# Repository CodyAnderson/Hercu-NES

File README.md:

# Hercu-NES
Hardware Exact Rough Clone Unto Nintendo Entertainment System

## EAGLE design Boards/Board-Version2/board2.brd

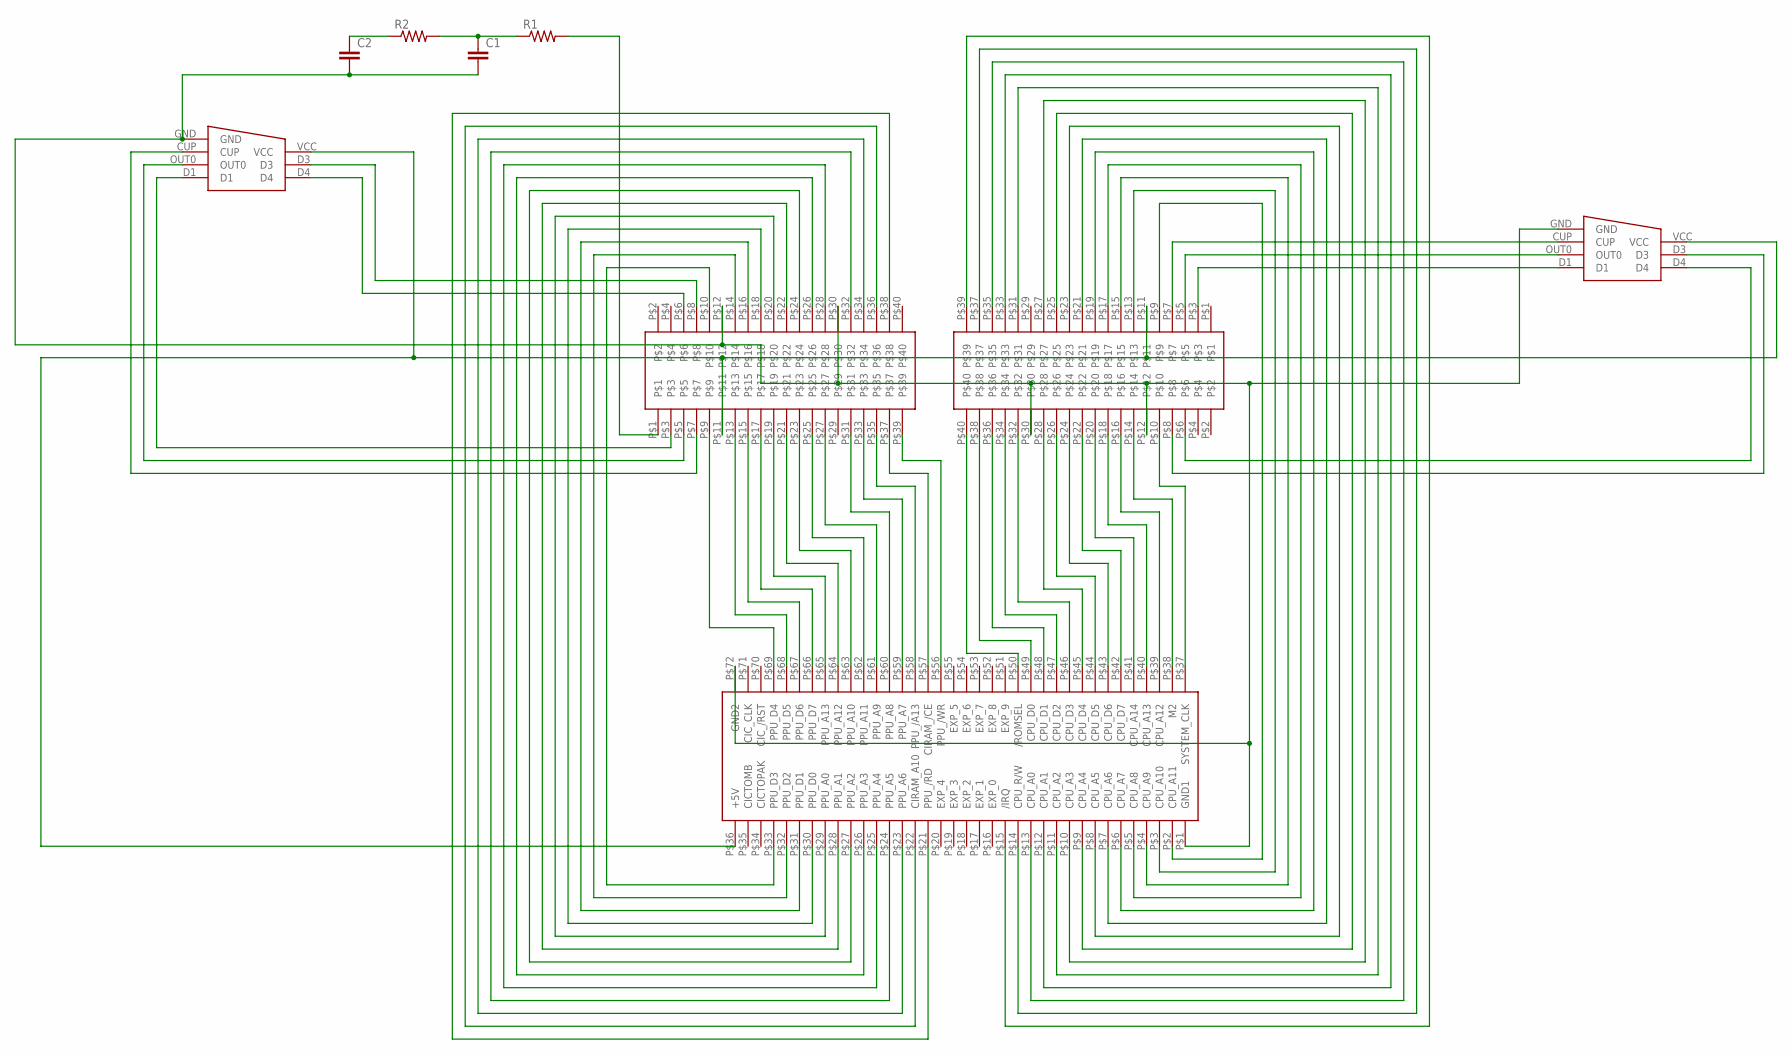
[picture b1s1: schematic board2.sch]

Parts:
C1, C2: C5/2.5; C5B2.5
R1, R2: R-US_0207/12; 0207/12
U$1: NES_CONN; 36X2
U$2, U$3: 40PINNER
U$4, U$5: 7CONN; 7CON

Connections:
+5V: U$1.P$36 (+5V), U$2.P$11, U$3.P$11, U$4.VCC, U$5.VCC
AUD: C2.1, R2.1
GND: C1.2, C2.2, U$1.P$1 (GND1), U$1.P$72 (GND2), U$2.P$12, U$2.P$30, U$3.P$12, U$3.P$30, U$4.GND, U$5.GND
unnamed: U$3.P$7, U$4.CUP
unnamed: U$1.P$2 (CPU_A11), U$3.P$9
unnamed: U$1.P$50 (/ROMSEL), U$3.P$40
unnamed: U$1.P$49 (CPU_D0), U$3.P$38
unnamed: U$1.P$3 (CPU_A10), U$3.P$13
unnamed: U$1.P$4 (CPU_A9), U$3.P$15
unnamed: U$1.P$48 (CPU_D1), U$3.P$36
unnamed: U$1.P$47 (CPU_D2), U$3.P$34
unnamed: U$1.P$46 (CPU_D3), U$3.P$32
unnamed: U$1.P$5 (CPU_A8), U$3.P$17
unnamed: U$1.P$6 (CPU_A7), U$3.P$19
unnamed: U$3.P$8, U$4.D3
unnamed: U$1.P$45 (CPU_D4), U$3.P$28
unnamed: U$1.P$44 (CPU_D5), U$3.P$26
unnamed: U$1.P$43 (CPU_D6), U$3.P$24
unnamed: U$1.P$42 (CPU_D7), U$3.P$22
unnamed: U$1.P$41 (CPU_A14), U$3.P$20
unnamed: U$1.P$40 (CPU_A13), U$3.P$18
unnamed: U$1.P$39 (CPU_A12), U$3.P$16
unnamed: U$1.P$38 (M2), U$3.P$14
unnamed: U$1.P$37 (SYSTEM_CLK), U$3.P$10
unnamed: U$3.P$5, U$4.OUT0
unnamed: U$1.P$7 (CPU_A6), U$3.P$21
unnamed: U$1.P$8 (CPU_A5), U$3.P$23
unnamed: U$1.P$9 (CPU_A4), U$3.P$25
unnamed: U$1.P$10 (CPU_A3), U$3.P$27
unnamed: U$1.P$11 (CPU_A2), U$3.P$31
unnamed: U$1.P$12 (CPU_A1), U$3.P$33
unnamed: U$1.P$13 (CPU_A0), U$3.P$35
unnamed: U$1.P$14 (CPU_R/W), U$3.P$37
unnamed: U$1.P$15 (/IRQ), U$3.P$39
unnamed: U$3.P$6, U$4.D4
unnamed: U$1.P$69 (PPU_D4), U$2.P$9
unnamed: U$1.P$68 (PPU_D5), U$2.P$13
unnamed: U$1.P$67 (PPU_D6), U$2.P$15
unnamed: U$1.P$66 (PPU_D7), U$2.P$17
unnamed: U$1.P$65 (PPU_A13), U$2.P$19
unnamed: U$1.P$64 (PPU_A12), U$2.P$21
unnamed: U$1.P$63 (PPU_A10), U$2.P$23
unnamed: U$1.P$62 (PPU_A11), U$2.P$25
unnamed: U$1.P$61 (PPU_A9), U$2.P$27
unnamed: U$1.P$60 (PPU_A8), U$2.P$31
unnamed: U$1.P$59 (PPU_A7), U$2.P$33
unnamed: U$1.P$58 (PPU_/A13), U$2.P$35
unnamed: U$1.P$57 (CIRAM_/CE), U$2.P$37
unnamed: U$1.P$56 (PPU_/WR), U$2.P$39
unnamed: U$3.P$3, U$4.D1
unnamed: U$2.P$8, U$5.D3
unnamed: U$1.P$33 (PPU_D3), U$2.P$10
unnamed: U$1.P$32 (PPU_D2), U$2.P$14
unnamed: U$1.P$31 (PPU_D1), U$2.P$16
unnamed: U$1.P$30 (PPU_D0), U$2.P$18
unnamed: U$1.P$29 (PPU_A0), U$2.P$20
unnamed: U$1.P$28 (PPU_A1), U$2.P$22
unnamed: U$1.P$27 (PPU_A2), U$2.P$24
unnamed: U$1.P$26 (PPU_A3), U$2.P$26
unnamed: U$1.P$25 (PPU_A4), U$2.P$28
unnamed: U$1.P$24 (PPU_A5), U$2.P$32
unnamed: U$1.P$23 (PPU_A6), U$2.P$34
unnamed: U$1.P$22 (CIRAM_A10), U$2.P$36
unnamed: U$1.P$21 (PPU_/RD), U$2.P$38
unnamed: U$2.P$6, U$5.D4
unnamed: U$2.P$7, U$5.CUP
unnamed: U$2.P$5, U$5.OUT0
unnamed: U$2.P$3, U$5.D1
unnamed: C1.1, R1.1, R2.2
unnamed: R1.2, U$2.P$1

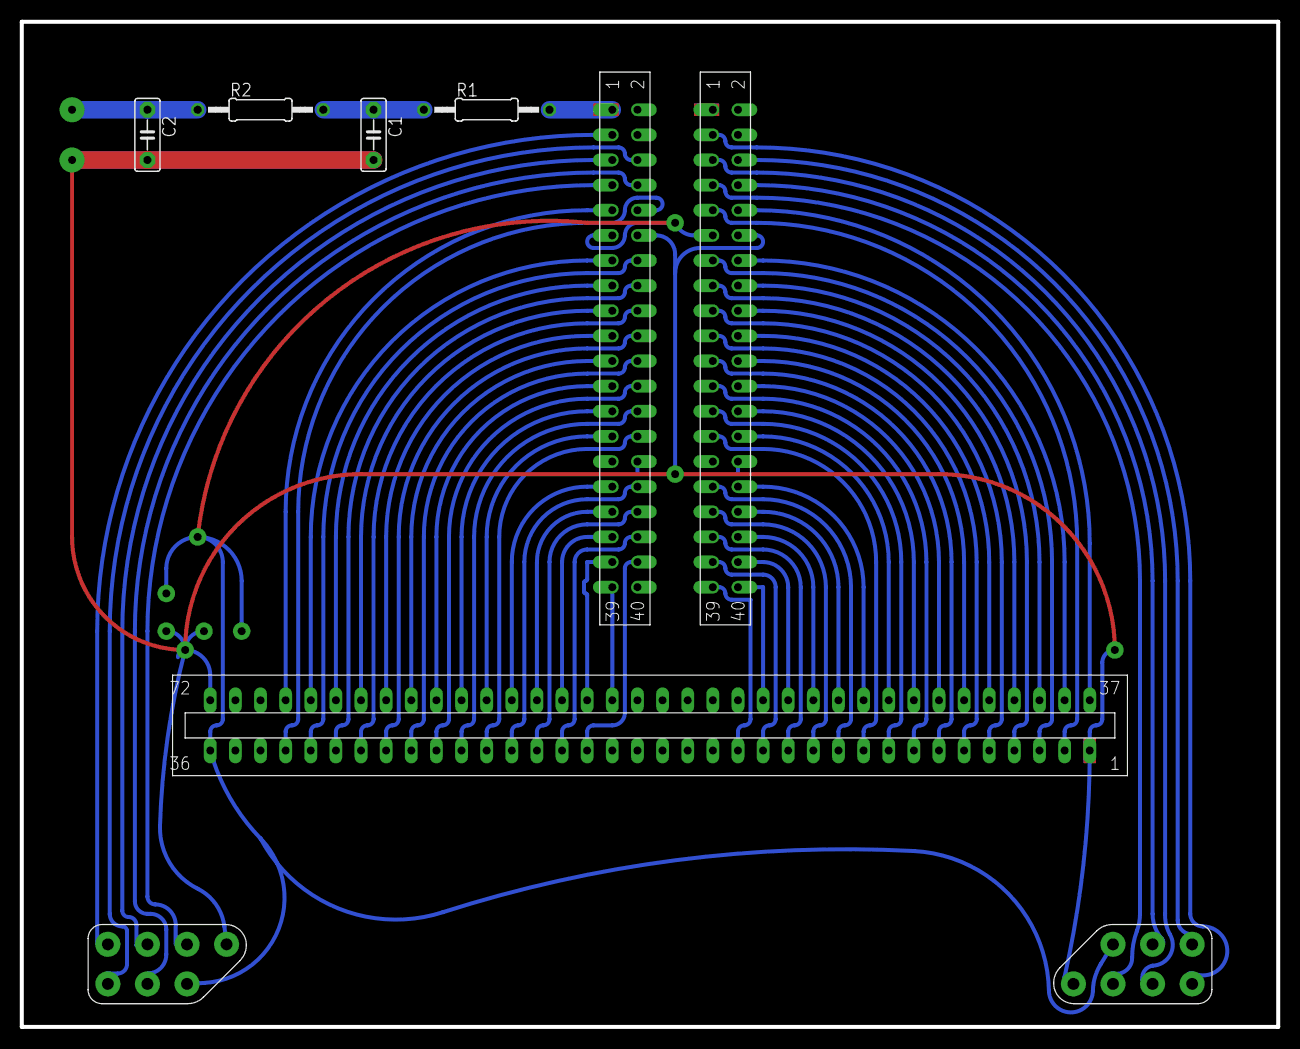
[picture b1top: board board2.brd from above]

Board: 2 copper layers, 127.0 x 101.6 mm, 9 parts (0 on the bottom side), 70 nets.

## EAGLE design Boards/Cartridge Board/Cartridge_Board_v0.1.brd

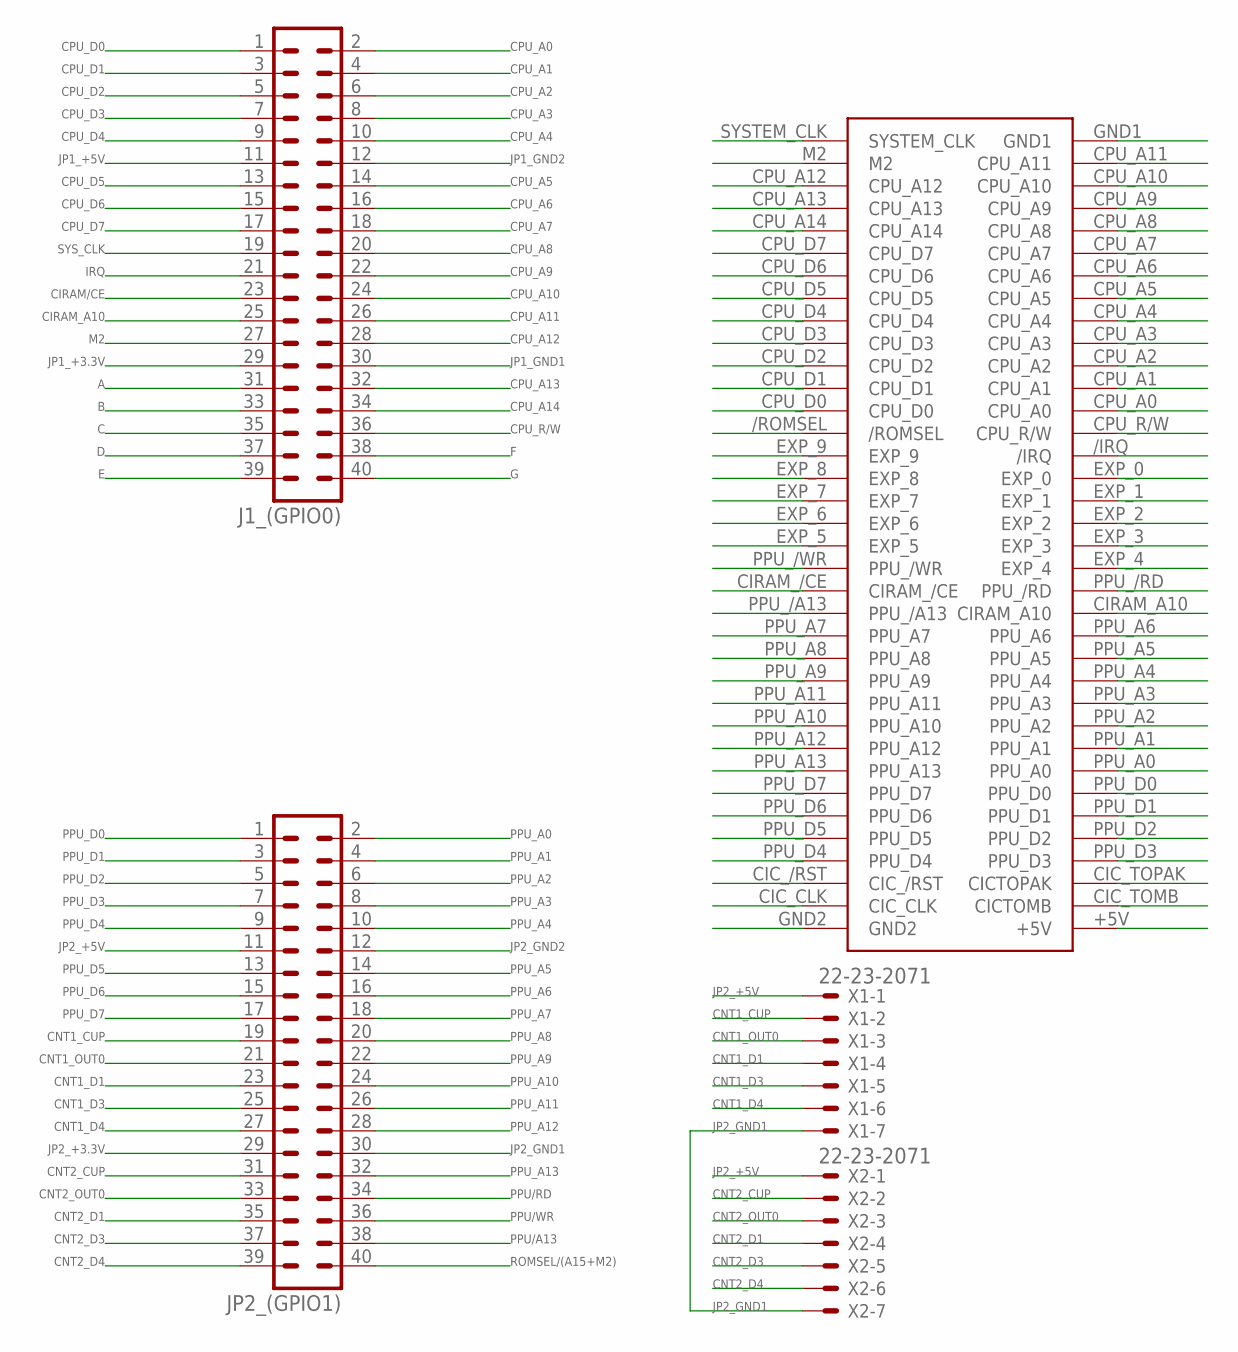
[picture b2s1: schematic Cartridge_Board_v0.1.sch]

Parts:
J1_(GPIO0): 40V
JP2_(GPIO1): 40V
U$1: CONNFEMALE72PIN0.1; 36X2
X1, X2: 22-23-2071

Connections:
A: J1_(GPIO0).31
B: J1_(GPIO0).33
C: J1_(GPIO0).35
CIRAM/CE: J1_(GPIO0).23, U$1.CIRAM_/CE
CIRAM_A10: J1_(GPIO0).25, U$1.CIRAM_A10
CNT1_CUP: JP2_(GPIO1).19, X1.2
CNT1_D1: JP2_(GPIO1).23, X1.4
CNT1_D3: JP2_(GPIO1).25, X1.5
CNT1_D4: JP2_(GPIO1).27, X1.6
CNT1_OUT0: JP2_(GPIO1).21, X1.3
CNT2_CUP: JP2_(GPIO1).31, X2.2
CNT2_D1: JP2_(GPIO1).35, X2.4
CNT2_D3: JP2_(GPIO1).37, X2.5
CNT2_D4: JP2_(GPIO1).39, X2.6
CNT2_OUT0: JP2_(GPIO1).33, X2.3
CPU_A0: J1_(GPIO0).2, U$1.CPU_A0
CPU_A1: J1_(GPIO0).4, U$1.CPU_A1
CPU_A2: J1_(GPIO0).6, U$1.CPU_A2
CPU_A3: J1_(GPIO0).8, U$1.CPU_A3
CPU_A4: J1_(GPIO0).10, U$1.CPU_A4
CPU_A5: J1_(GPIO0).14, U$1.CPU_A5
CPU_A6: J1_(GPIO0).16, U$1.CPU_A6
CPU_A7: J1_(GPIO0).18, U$1.CPU_A7
CPU_A8: J1_(GPIO0).20, U$1.CPU_A8
CPU_A9: J1_(GPIO0).22, U$1.CPU_A9
CPU_A10: J1_(GPIO0).24, U$1.CPU_A10
CPU_A11: J1_(GPIO0).26, U$1.CPU_A11
CPU_A12: J1_(GPIO0).28, U$1.CPU_A12
CPU_A13: J1_(GPIO0).32, U$1.CPU_A13
CPU_A14: J1_(GPIO0).34, U$1.CPU_A14
CPU_D0: J1_(GPIO0).1, U$1.CPU_D0
CPU_D1: J1_(GPIO0).3, U$1.CPU_D1
CPU_D2: J1_(GPIO0).5, U$1.CPU_D2
CPU_D3: J1_(GPIO0).7, U$1.CPU_D3
CPU_D4: J1_(GPIO0).9, U$1.CPU_D4
CPU_D5: J1_(GPIO0).13, U$1.CPU_D5
CPU_D6: J1_(GPIO0).15, U$1.CPU_D6
CPU_D7: J1_(GPIO0).17, U$1.CPU_D7
CPU_R/W: J1_(GPIO0).36, U$1.CPU_R/W
D: J1_(GPIO0).37
E: J1_(GPIO0).39
F: J1_(GPIO0).38
G: J1_(GPIO0).40
IRQ: J1_(GPIO0).21, U$1./IRQ
JP1_+3.3V: J1_(GPIO0).29
JP1_+5V: J1_(GPIO0).11
JP1_GND1: J1_(GPIO0).30, U$1.GND1, U$1.GND2
JP1_GND2: J1_(GPIO0).12
JP2_+3.3V: JP2_(GPIO1).29
JP2_+5V: JP2_(GPIO1).11, U$1.+5V, X1.1, X2.1
JP2_GND1: JP2_(GPIO1).30, X1.7, X2.7
JP2_GND2: JP2_(GPIO1).12
M2: J1_(GPIO0).27, U$1.M2
PPU/A13: JP2_(GPIO1).38, U$1.PPU_/A13
PPU/RD: JP2_(GPIO1).34, U$1.PPU_/RD
PPU/WR: JP2_(GPIO1).36, U$1.PPU_/WR
PPU_A0: JP2_(GPIO1).2, U$1.PPU_A0
PPU_A1: JP2_(GPIO1).4, U$1.PPU_A1
PPU_A2: JP2_(GPIO1).6, U$1.PPU_A2
PPU_A3: JP2_(GPIO1).8, U$1.PPU_A3
PPU_A4: JP2_(GPIO1).10, U$1.PPU_A4
PPU_A5: JP2_(GPIO1).14, U$1.PPU_A5
PPU_A6: JP2_(GPIO1).16, U$1.PPU_A6
PPU_A7: JP2_(GPIO1).18, U$1.PPU_A7
PPU_A8: JP2_(GPIO1).20, U$1.PPU_A8
PPU_A9: JP2_(GPIO1).22, U$1.PPU_A9
PPU_A10: JP2_(GPIO1).24, U$1.PPU_A10
PPU_A11: JP2_(GPIO1).26, U$1.PPU_A11
PPU_A12: JP2_(GPIO1).28, U$1.PPU_A12
PPU_A13: JP2_(GPIO1).32, U$1.PPU_A13
PPU_D0: JP2_(GPIO1).1, U$1.PPU_D0
PPU_D1: JP2_(GPIO1).3, U$1.PPU_D1
PPU_D2: JP2_(GPIO1).5, U$1.PPU_D2
PPU_D3: JP2_(GPIO1).7, U$1.PPU_D3
PPU_D4: JP2_(GPIO1).9, U$1.PPU_D4
PPU_D5: JP2_(GPIO1).13, U$1.PPU_D5
PPU_D6: JP2_(GPIO1).15, U$1.PPU_D6
PPU_D7: JP2_(GPIO1).17, U$1.PPU_D7
ROMSEL/(A15+M2): JP2_(GPIO1).40, U$1./ROMSEL
SYS_CLK: J1_(GPIO0).19, U$1.SYSTEM_CLK

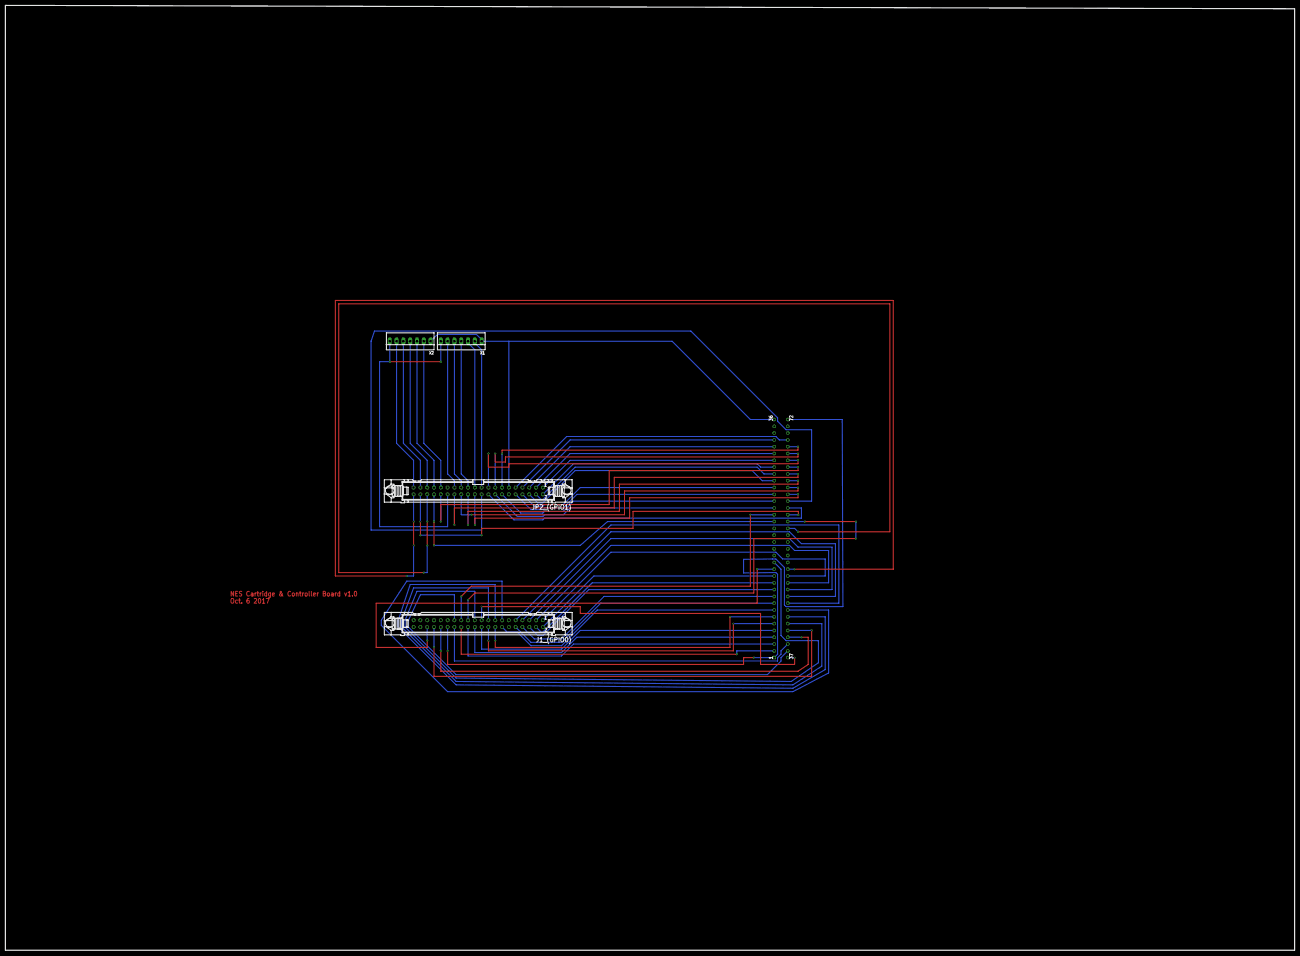
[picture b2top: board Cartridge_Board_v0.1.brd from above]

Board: 2 copper layers, 481.3 x 352.7 mm, 6 parts (0 on the bottom side), 68 nets.

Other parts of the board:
DRILEGEND: DRILEGEND

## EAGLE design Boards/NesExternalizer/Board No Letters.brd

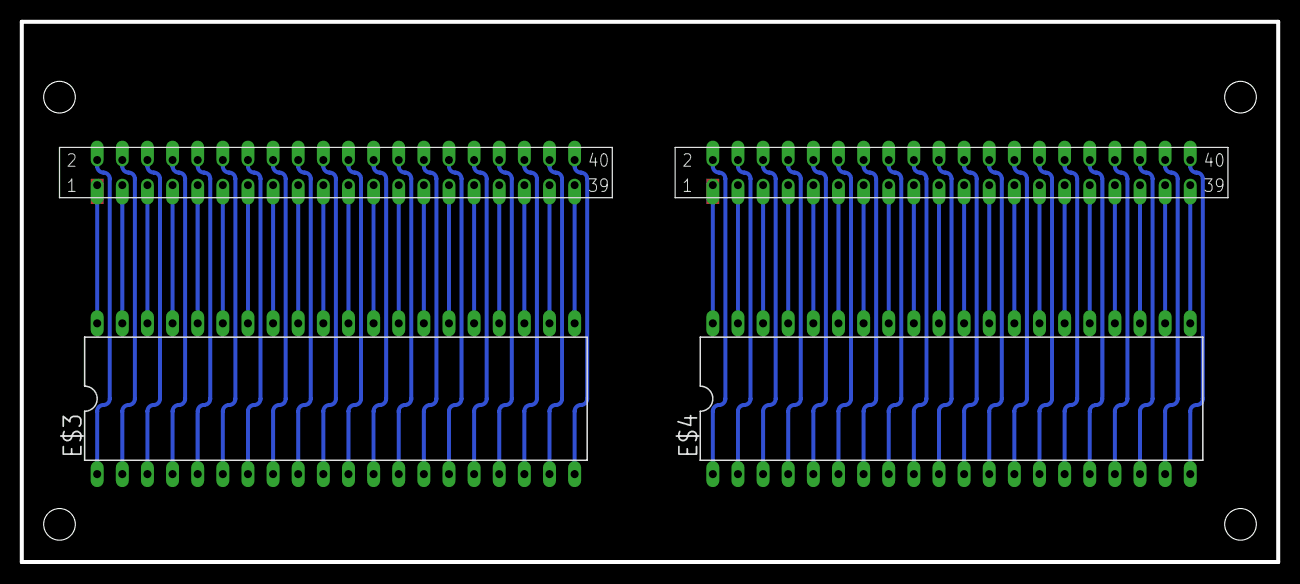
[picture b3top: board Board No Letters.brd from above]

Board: 2 copper layers, 127.0 x 54.6 mm, 4 parts (0 on the bottom side), 42 nets.

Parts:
E$1, E$2: 40PINNER
E$3, E$4: DIL40

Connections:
S$1: E$1.P$2, E$3.1
S$21: E$1.P$1, E$3.40
S$22: E$1.P$3, E$3.39
S$23: E$1.P$5, E$3.38
S$24: E$1.P$7, E$3.37
S$25: E$1.P$9, E$3.36
S$26: E$1.P$11, E$3.35
S$27: E$1.P$13, E$3.34
S$28: E$1.P$15, E$3.33
S$29: E$1.P$17, E$3.32
S$30: E$1.P$19, E$3.31
S$31: E$1.P$21, E$3.30
S$32: E$1.P$23, E$3.29
S$33: E$1.P$25, E$3.28
S$34: E$1.P$27, E$3.27
S$35: E$1.P$29, E$3.26
S$36: E$1.P$31, E$3.25
S$37: E$1.P$33, E$3.24
S$38: E$1.P$35, E$3.23
S$39: E$1.P$37, E$3.22
S$40: E$1.P$39, E$3.21
S$41: E$2.P$2, E$4.1
S$61: E$2.P$1, E$4.40
S$62: E$2.P$3, E$4.39
S$63: E$2.P$5, E$4.38
S$64: E$2.P$7, E$4.37
S$65: E$2.P$9, E$4.36
S$66: E$2.P$11, E$4.35
S$67: E$2.P$13, E$4.34
S$68: E$2.P$15, E$4.33
S$69: E$2.P$17, E$4.32
S$70: E$2.P$19, E$4.31
S$71: E$2.P$21, E$4.30
S$72: E$2.P$23, E$4.29
S$73: E$2.P$25, E$4.28
S$74: E$2.P$27, E$4.27
S$75: E$2.P$29, E$4.26
S$76: E$2.P$31, E$4.25
S$77: E$2.P$33, E$4.24
S$78: E$2.P$35, E$4.23
S$79: E$2.P$37, E$4.22
S$80: E$2.P$39, E$4.21

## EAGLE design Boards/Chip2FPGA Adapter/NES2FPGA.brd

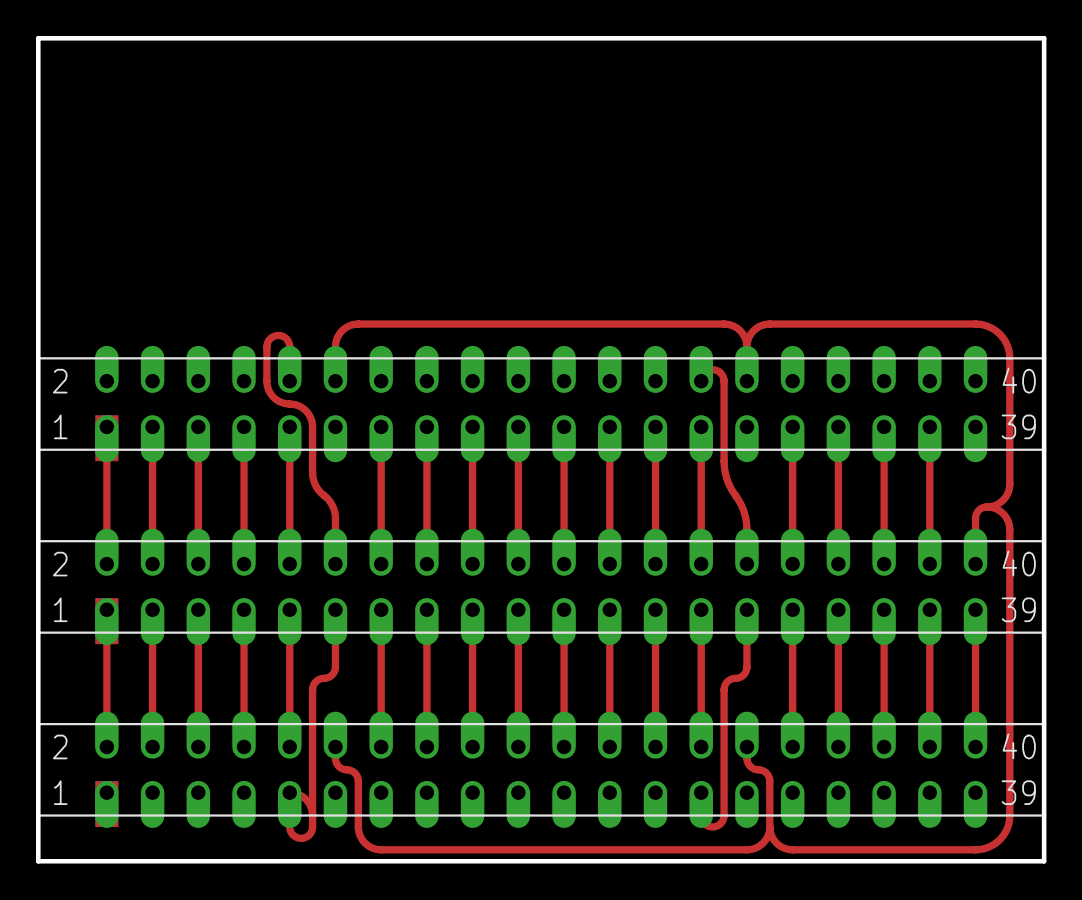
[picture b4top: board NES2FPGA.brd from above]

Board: 2 copper layers, 55.9 x 45.7 mm, 3 parts (0 on the bottom side), 40 nets.

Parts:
E$1, E$2, E$3: 40PINNER

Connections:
S$1: E$1.P$12, E$1.P$30, E$2.P$12, E$2.P$30, E$3.P$40
S$2: E$1.P$9, E$3.P$11
S$3: E$1.P$27, E$3.P$29
S$4: E$2.P$10, E$3.P$12
S$5: E$2.P$28, E$3.P$30
S$6: E$1.P$2, E$3.P$1
S$7: E$1.P$4, E$3.P$3
S$8: E$1.P$6, E$3.P$5
S$9: E$1.P$8, E$3.P$7
S$10: E$1.P$10, E$3.P$9
S$11: E$1.P$14, E$3.P$13
S$12: E$1.P$16, E$3.P$15
S$13: E$1.P$18, E$3.P$17
S$14: E$1.P$20, E$3.P$19
S$15: E$1.P$22, E$3.P$21
S$16: E$1.P$24, E$3.P$23
S$17: E$1.P$26, E$3.P$25
S$18: E$1.P$28, E$3.P$27
S$19: E$1.P$32, E$3.P$31
S$20: E$1.P$34, E$3.P$33
S$21: E$1.P$36, E$3.P$35
S$22: E$1.P$38, E$3.P$37
S$23: E$1.P$40, E$3.P$39
S$24: E$2.P$1, E$3.P$2
S$25: E$2.P$3, E$3.P$4
S$26: E$2.P$5, E$3.P$6
S$27: E$2.P$7, E$3.P$8
S$28: E$2.P$9, E$3.P$10
S$29: E$2.P$13, E$3.P$14
S$30: E$2.P$15, E$3.P$16
S$31: E$2.P$17, E$3.P$18
S$32: E$2.P$19, E$3.P$20
S$33: E$2.P$21, E$3.P$22
S$34: E$2.P$23, E$3.P$24
S$35: E$2.P$25, E$3.P$26
S$36: E$2.P$27, E$3.P$28
S$37: E$2.P$31, E$3.P$32
S$38: E$2.P$33, E$3.P$34
S$39: E$2.P$35, E$3.P$36
S$40: E$2.P$37, E$3.P$38

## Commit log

2017-10-04 Project structure and placeholder files
    Added folder structure to the project directory
    Added placeholder files to force git to see the folders
    Edited the README to see what would happen
2017-10-04 More README tests
    bolded the README test line
2017-10-04 Fixed README tag issue and made my own branch
    Fixed (?) the html tag fro bold I was testing in
    I've gotta stop testing on master haha
2017-10-04 Same
    same
2017-10-04 Reset the README
    Reset the README for professionality reasons.
    Will re-update it when real README is complete.
2017-10-06 Added FPGA Files
    These are mostly untested... the templates should be good.
2017-10-08 Added proposal paper
    Added the files to recreate the proposal paper, as well as the rendered
    pdf of the proposal paper
2017-10-08 Some more proposal paper material
2017-10-10 Cartridge Board it's here, 2 4 1 D-eel Spicy Hot
    Its the board AAH
2017-10-10 SLoW AnD STEaDY
    wins the rase
2017-10-10 This is the equialivant of a suicide note for a commit
2017-10-15 Constraints Working
    Constraints Describing the Cartridge and controller pins have been made.
2017-10-15 Added Board
    Added the current board and schematic for the periperal connections.
2017-10-15 Renamed Folder
    Renamed
2017-10-15 ROM Dump folder
    Added a rom dump folder along with a script to merge iNES header, PROG
    ROM and CHAR ROM into an emulation read ROM
    Correct header and ROM dumps still needed
2017-10-15 Added Header
    Added correct iNES header for Mario given ROM sizes and other cart
    variables
2017-10-15 Fixed merging script
2017-10-16 Fixed CHAR ROM and correct header
    Fixed CHAR ROM and correct header
    Fully working ROM
    Added gifs of before/after
2017-10-16 Added hex version of ROMDUMP
2017-10-17 Added a CPU
    It has only one instruction tho, so don't be too impressed 😒
2017-10-24 Case statements
    computeriy
2017-10-24 Added internal CPR registers
    Added internal CPR registers as wel as began to add some more CPU structure which was missing.
2017-10-24 bump
2017-10-25 Did some OP C O D E S
    It was alright
2017-11-01 Some minute progress (?)
2017-11-07 Summary
    Description
2017-11-07 updated board a little
    did some updates to the pcb
2017-11-14 Bump
    indeed
2017-11-16 Doing some work on the PPU
2017-11-19 Added some stuff
    please don't hurt me
2017-11-19 summary
    alright
2017-11-19 stuff
2017-11-19 Micromerge boardstuff
2017-11-19 micromerge cpu project
2017-11-19 micromerge jsim+misc
2017-11-20 Now That's What I Call a CPU 82™
2017-11-20 Acts more like an NES
    Now the parameter CPU_RESET_ADDRESS points to a location where the
    address of the first instruction is. The CPU automatically loads in the
    first two bytes at the location of the macro and then jumps there. It
    may or may not be a hack where I just trick the CPU into executing an
    actual jump command, but a processor is just a rock we trick into
    thinking, so don't judge me too hard.
2017-11-20 Added some more instructions
    somewhat haphazardly
2017-11-20 Small Simulation Changes
2017-11-20 Added Proposal Paper Revision
2017-11-20 Typed like a few lines, now we are going to both be the cody
    you know whats up
2017-11-21 pictures go out
    pictures out go
2017-11-21 Tested Out the test program in an NES emulator
    (It worked alright)
2017-11-27 Made a task, made a mistake, the story of CPU boy
2017-11-28 tasks dont work
2017-11-29 Made Logic Analyser and Captured data.
    The data is in the zip in rom dumps. It is a lot of cpu data.
2017-12-11 Capture Analyze
    Added code to capture and analyze cpu and ppu. Also there are captures in here.
2017-12-11 ignore
    pls ignore
2017-12-11 pls work2
    WORK
2017-12-11 pls work3
    WORK
    !!!!!
2017-12-11 pls5
    work
2017-12-11 submitting scrolling ppu
    scrolling!
2017-12-11 cleaning
    cleaning
2018-01-18 Made folder for drawIO
    Put some diagrams in there.
2018-01-25 Added Timeline to GitHub
    Added Timeline
2018-02-02 We doin it again
    yeehaw
2018-02-23 Tried to fix extraneously included Eagle board files.
2018-02-23 Added a newline to then end of the .gitignore file.
2018-02-23 Created a vivado project to include all of the modules into a mega project
2018-02-23 Tweaked Folder structure
2018-02-23 added placeholder files
2018-02-23 Folder structure re-arranged
2018-02-26 NES-PPU-DropIn: Project Creation
2018-02-26 Added documents from old project.
2018-02-26 Added Boards and an Eagle Library
2018-03-01 Added NTSC video output to the PPU project.
2018-03-23 What once was working but now is not.
2018-03-23 Added the beginnings of the sequencer decoder (IE the decode ROM)
2018-03-23 the goods have reached the destination.
2018-03-24 Let's lego all these CPU chunks into a CPU
2018-03-30 Mostly Working, Still really crashy though
2018-04-01 Added VGA output, made less crashy.
2018-04-05 i did a naughty Owo~
2018-04-05 ALL ABORD THE VANGABUS
2018-04-05 yooooooooooooooooooooooooooooooooooooooooooooooooooooooooooooooooooooooooooooooooooooooooooooooooooooooooooooooooooooooooooooooooooooooooo
2018-04-05 Fixed more bugs!
2018-04-14 Started the poster, made some vectorized mario stuff.
2018-04-14 Fixed many bugs with the sprites.
2018-04-19 Made Logo EYE POPPING!
2018-04-21 Done some poster stuff
2018-04-21 Made many changes to the poster, also started a different style that may want to be explored.
2018-04-21 We still tryin'
2018-04-21 Well, Cody's done it now
2018-04-21 Please pretend this didn't happen
2018-04-22 Made some updates to the poster
2018-04-22 Added to poster
2018-04-22 simulation screenshot
2018-04-22 Poster and pals
2018-04-22 Testing if I can now commit again :(
2018-04-22 Cleaning up that little test
2018-04-22 Updating the diagram
2018-04-22 Some more things on the poster
2018-04-22 Visibility
2018-04-22 Money
2018-04-22 more updates... not fully done yet
2018-04-22 I'm slapping the done sticker on it.
2018-04-22 6502 Diagram done. Let's get this old girl oiled up and put her to bed wet.
2018-04-22 The poster is completed
2018-04-23 Okay, fixed the incorrect render size. The poster is now done.
2018-04-23 Added clipping mask to keep the traces from leaving the board
2018-08-02 Created the data bus handler. This handles all of the data busses and their interaction internally with the pass mosfets that combine data busses together and the drain mosfets. All of the code writt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
